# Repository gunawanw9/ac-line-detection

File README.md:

# [AC mains/ Zero Crossing Detection Module](https://shop.edwinrobotics.com/sensors/960-ac-mains-zero-crossing-detection-module.html) #

The AC mains/ Zero Crossing Detection Module from Edwin Robotics is an optically isolated AC line-to-logic interface device. The AC line voltage is monitored by a rectifier and an optocoupler, which provides isolation between High Voltage (HV) and Low Voltage (LV) Side. An active AC power line drives the output gate of the optocoupler to a logic low condition and in the absence of an AC line the output remains HIGH. The board is designed solely for the use as an AC line monitor. By default the output of the optocoupler is connected to a 2.2uF capacitor to provide TTL output, in the event that zero crossing is required, a jumper trace on the back of the PCB will need to be cut. Check the hookup guide for more information. The board has an on board pull-up resistors for uses with microcontrollers with weak pull-up. 

**FEATURES:**

* AC mains & Zero Crossing detection.
* On board pull-up
* High voltage isolation between input and output.
* Logic level compatibility

**SPECIFICATION:**

* Input Voltage Range: 110-300 V AC
* Max. Output Voltage Range: 5V
* Logic Interface: VCC, GND, Signal
* Dimensions: 20x20mm

**DOCUMENTS:**

[Hookup Guide](http://learn.edwinrobotics.com/230v110v-ac-mains-detection-using-arduino-raspberry-pi-and-esp8266-thing/)

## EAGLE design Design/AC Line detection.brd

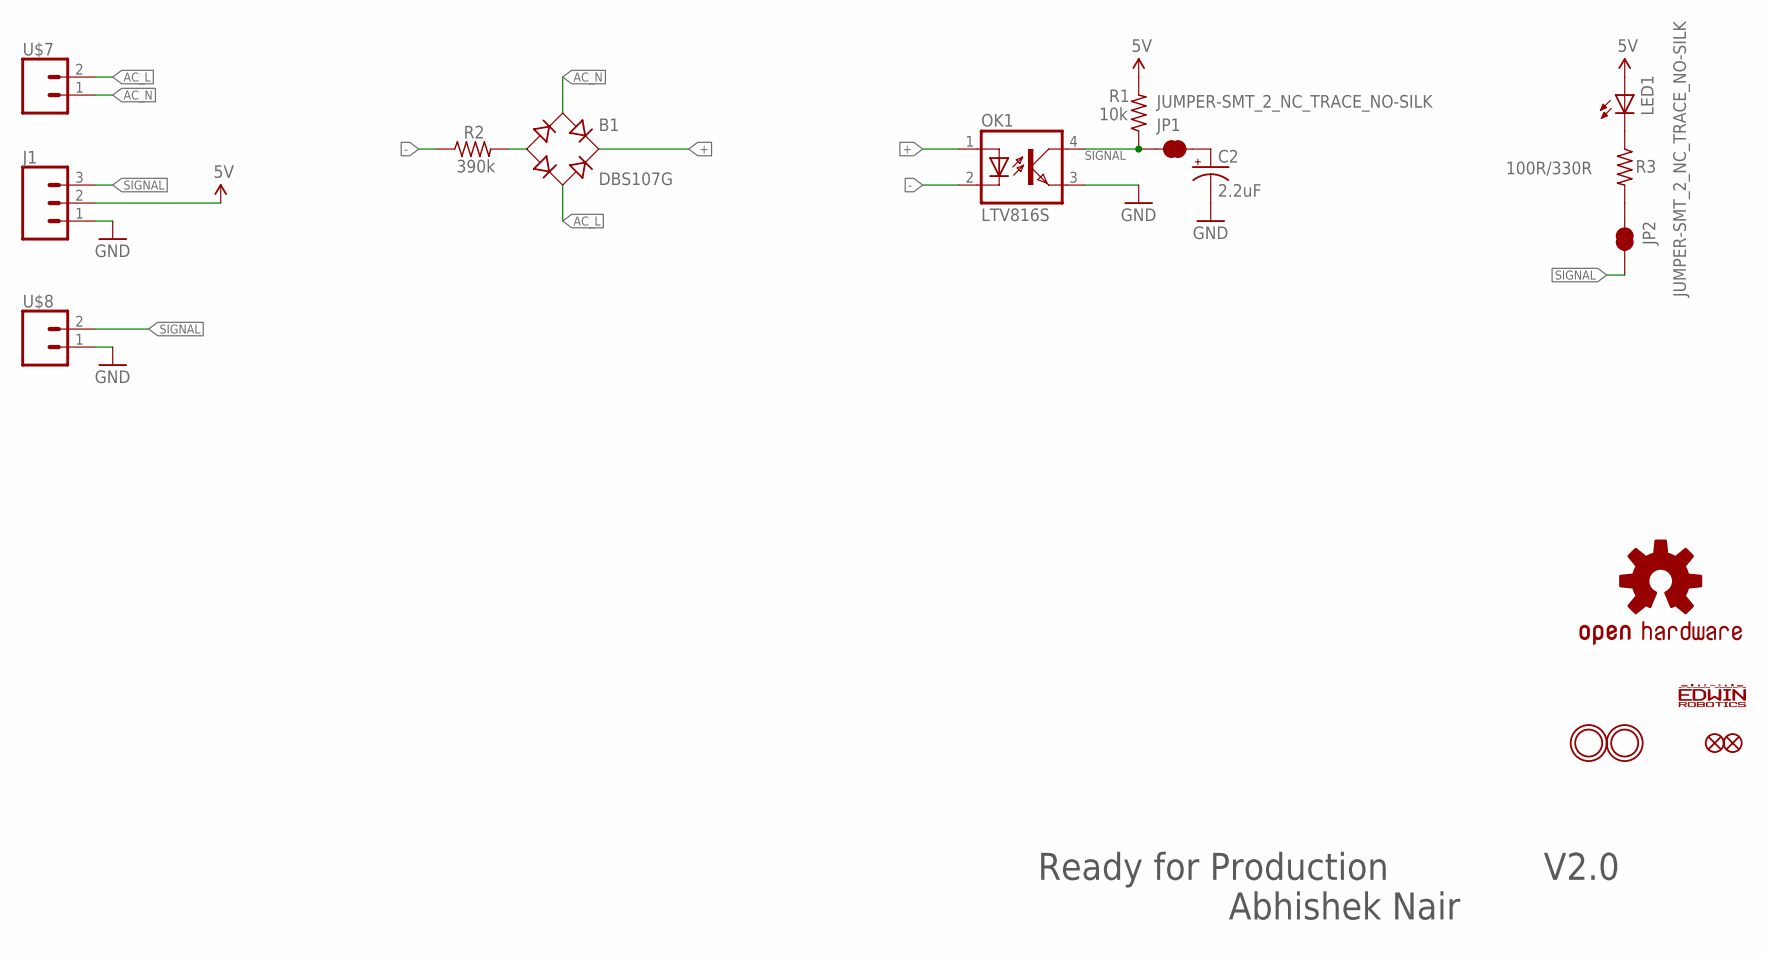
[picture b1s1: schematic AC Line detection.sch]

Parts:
B1: DBS107G; DBS
C2: 2.2uF; CAPACITOR-2.2UF_4X5MM_JENNY
FID1, FID2: FIDUCIAL""; FIDUCIAL_1MM
J1: CONN_03; 1X03
JP1, JP2: JUMPER-SMT_2_NC_TRACE_NO-SILK; SMT-JUMPER_2_NC_TRACE_NO-SILK
LED1: LED_TH/SMDCHIPLED_0603; CHIPLED_0603
LOGO1: OSHW-LOGOMINI; OSHW-LOGO-MINI
OK1: LTV816S; DIL4-SMD
R1: 10k; R0603
R2: 390k; R0603
R3: 100R/330R; R0603
U$1: LOGO-9.5MMX4.5MM
U$5, U$6: MOUNTINGHOLE3.0THIN; MOUNTINGHOLE_3.0_PLATEDTHIN
U$7, U$8: SCREW_TERMINALS-2P-5MM; W237-102

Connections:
5V: J1.2, LED1.A, R1.2
+: B1.+, OK1.1 (A)
-: OK1.2 (C), R2.1
AC_L: B1.AC2, U$7.2
AC_N: B1.AC1, U$7.1
GND: C2.-, J1.1, OK1.3 (EMIT), U$8.1
unnamed: B1.-, R2.2
unnamed: C2.+, JP1.2
unnamed: LED1.C, R3.1
unnamed: JP2.1, R3.2
SIGNAL: J1.3, JP1.1, JP2.2, OK1.4 (COL), R1.1, U$8.2

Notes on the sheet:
Ready for Production
V2.0
Abhishek Nair

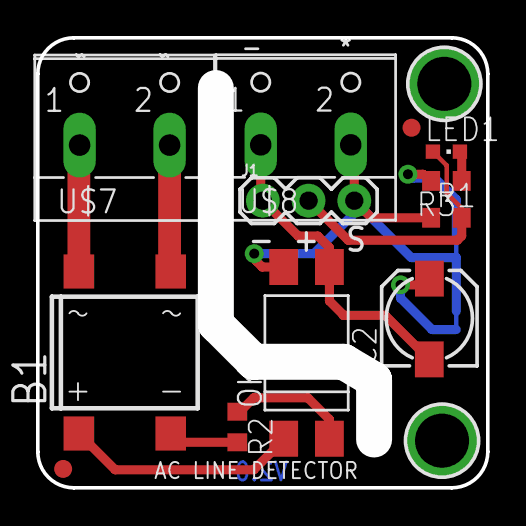
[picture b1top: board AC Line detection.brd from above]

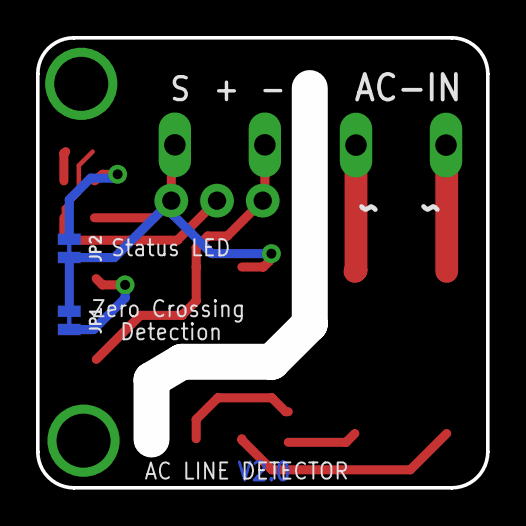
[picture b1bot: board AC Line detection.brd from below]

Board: 2 copper layers, 25.0 x 25.0 mm, 18 parts (4 on the bottom side), 11 nets.

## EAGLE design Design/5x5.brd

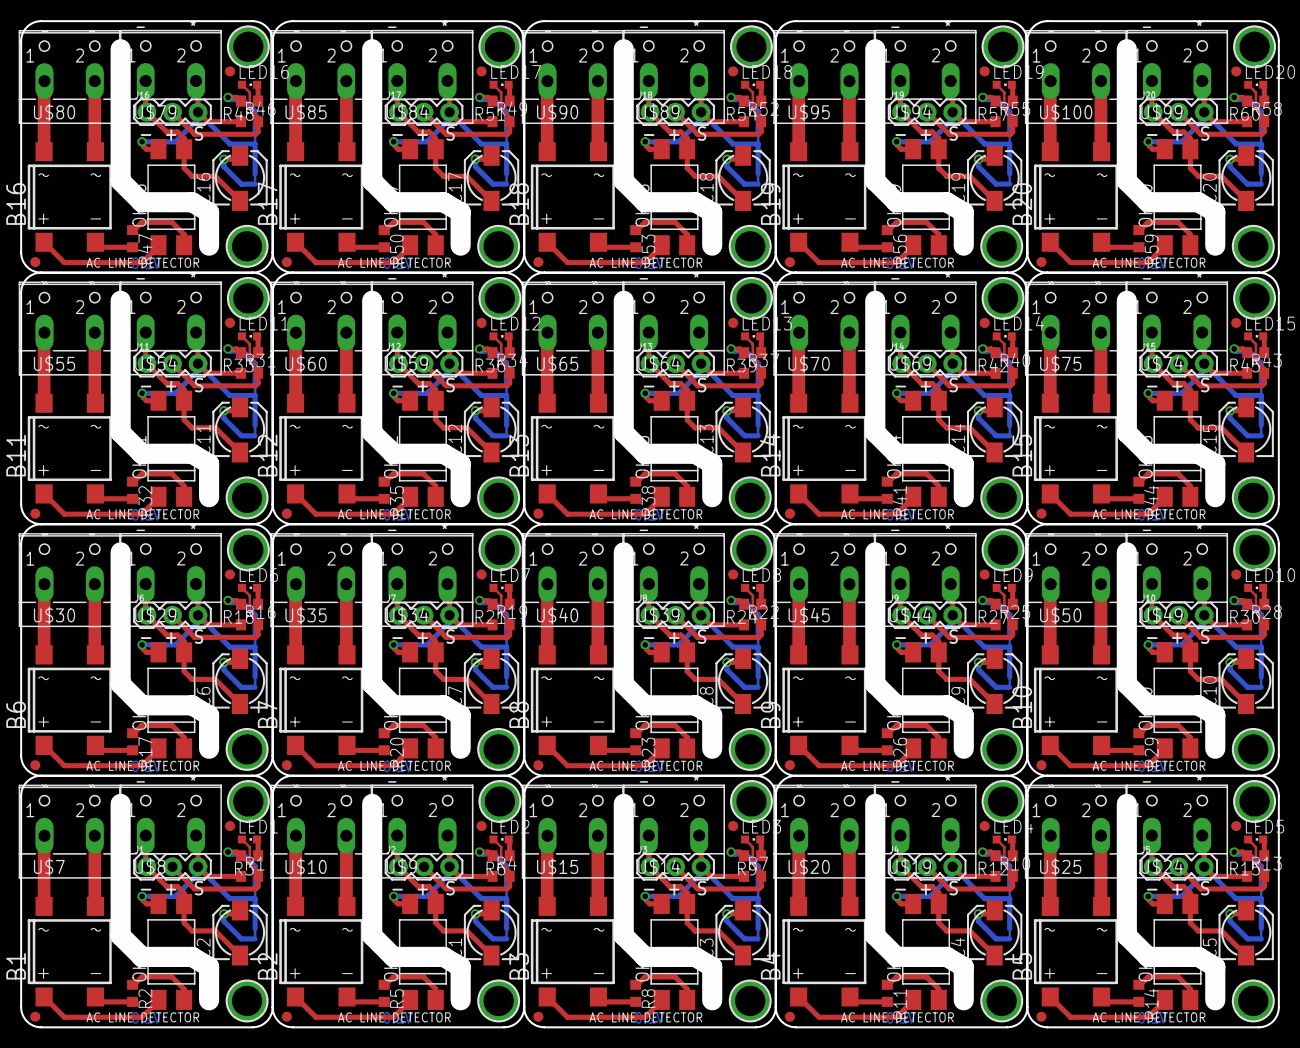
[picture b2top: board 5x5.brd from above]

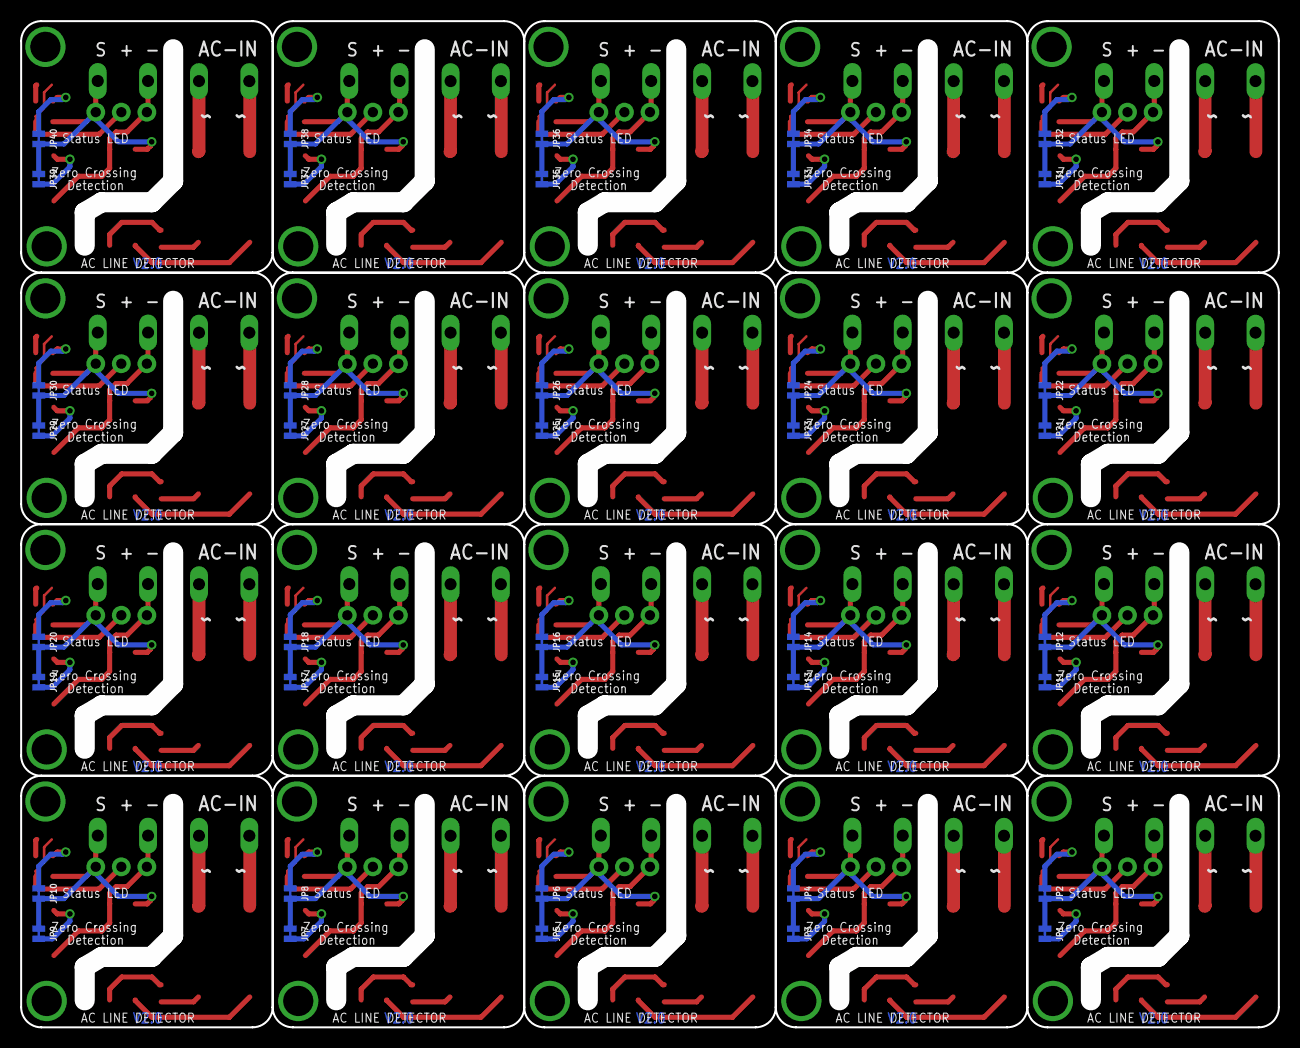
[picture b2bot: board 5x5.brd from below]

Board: 2 copper layers, 125.0 x 100.0 mm, 360 parts (80 on the bottom side), 220 nets.

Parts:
B1, B2, B3, B4, B5, B6, B7, B8, B9, B10, B11, B12, B13, B14, B15, B16, B17, B18, B19, B20: DBS107G; DBS
C1, C2, C3, C4, C5, C6, C7, C8, C9, C10, C11, C12, C13, C14, C15, C16, C17, C18, C19, C20: 2.2uF; CAPACITOR-2.2UF_4X5MM_JENNY
FID1, FID2, FID3, FID4, FID5, FID6, FID7, FID8, FID9, FID10, FID11, FID12, FID13, FID14, FID15, FID16, FID17, FID18, FID19, FID20, FID21, FID22, FID23, FID24, FID25, FID26, FID27, FID28, FID29, FID30, FID31, FID32, FID33, FID34, FID35, FID36, FID37, FID38, FID39, FID40: FIDUCIAL""; FIDUCIAL_1MM
J1, J2, J3, J4, J5, J6, J7, J8, J9, J10, J11, J12, J13, J14, J15, J16, J17, J18, J19, J20: 1X03
JP1, JP2, JP3, JP4, JP5, JP6, JP7, JP8, JP9, JP10, JP11, JP12, JP13, JP14, JP15, JP16, JP17, JP18, JP19, JP20, JP21, JP22, JP23, JP24, JP25, JP26, JP27, JP28, JP29, JP30, JP31, JP32, JP33, JP34, JP35, JP36, JP37, JP38, JP39, JP40: JUMPER-SMT_2_NC_TRACE_NO-SILK; SMT-JUMPER_2_NC_TRACE_NO-SILK
LED1, LED2, LED3, LED4, LED5, LED6, LED7, LED8, LED9, LED10, LED11, LED12, LED13, LED14, LED15, LED16, LED17, LED18, LED19, LED20: CHIPLED_0603
LOGO1, LOGO2, LOGO3, LOGO4, LOGO5, LOGO6, LOGO7, LOGO8, LOGO9, LOGO10, LOGO11, LOGO12, LOGO13, LOGO14, LOGO15, LOGO16, LOGO17, LOGO18, LOGO19, LOGO20: OSHW-LOGOMINI; OSHW-LOGO-MINI
OK1, OK2, OK3, OK4, OK5, OK6, OK7, OK8, OK9, OK10, OK11, OK12, OK13, OK14, OK15, OK16, OK17, OK18, OK19, OK20: LTV816S; DIL4-SMD
R1, R4, R7, R10, R13, R16, R19, R22, R25, R28, R31, R34, R37, R40, R43, R46, R49, R52, R55, R58: 10k; R0603
R2, R5, R8, R11, R14, R17, R20, R23, R26, R29, R32, R35, R38, R41, R44, R47, R50, R53, R56, R59: 390k; R0603
R3, R6, R9, R12, R15, R18, R21, R24, R27, R30, R33, R36, R39, R42, R45, R48, R51, R54, R57, R60: 100R/330R; R0603
U$1, U$2, U$11, U$16, U$21, U$26, U$31, U$36, U$41, U$46, U$51, U$56, U$61, U$66, U$71, U$76, U$81, U$86, U$91, U$96: LOGO-9.5MMX4.5MM
U$3, U$4, U$5, U$6, U$12, U$13, U$17, U$18, U$22, U$23, U$27, U$28, U$32, U$33, U$37, U$38, U$42, U$43, U$47, U$48, U$52, U$53, U$57, U$58, U$62, U$63, U$67, U$68, U$72, U$73, U$77, U$78, U$82, U$83, U$87, U$88, U$92, U$93, U$97, U$98: MOUNTINGHOLE3.0THIN; MOUNTINGHOLE_3.0_PLATEDTHIN
U$7, U$8, U$9, U$10, U$14, U$15, U$19, U$20, U$24, U$25, U$29, U$30, U$34, U$35, U$39, U$40, U$44, U$45, U$49, U$50, U$54, U$55, U$59, U$60, U$64, U$65, U$69, U$70, U$74, U$75, U$79, U$80, U$84, U$85, U$89, U$90, U$94, U$95, U$99, U$100: SCREW_TERMINALS-2P-5MM; W237-102

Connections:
5V: J1.2, LED1.A, R1.2
5V1: J2.2, LED2.A, R4.2
5V2: J3.2, LED3.A, R7.2
5V3: J4.2, LED4.A, R10.2
5V4: J5.2, LED5.A, R13.2
5V5: J6.2, LED6.A, R16.2
5V6: J7.2, LED7.A, R19.2
5V7: J8.2, LED8.A, R22.2
5V8: J9.2, LED9.A, R25.2
5V9: J10.2, LED10.A, R28.2
5V10: J11.2, LED11.A, R31.2
5V11: J12.2, LED12.A, R34.2
5V12: J13.2, LED13.A, R37.2
5V13: J14.2, LED14.A, R40.2
5V14: J15.2, LED15.A, R43.2
5V15: J16.2, LED16.A, R46.2
5V16: J17.2, LED17.A, R49.2
5V17: J18.2, LED18.A, R52.2
5V18: J19.2, LED19.A, R55.2
5V19: J20.2, LED20.A, R58.2
+: B1.+, OK1.1
+1: B2.+, OK2.1
+2: B3.+, OK3.1
+3: B4.+, OK4.1
+4: B5.+, OK5.1
+5: B6.+, OK6.1
+6: B7.+, OK7.1
+7: B8.+, OK8.1
+8: B9.+, OK9.1
+9: B10.+, OK10.1
+10: B11.+, OK11.1
+11: B12.+, OK12.1
+12: B13.+, OK13.1
+13: B14.+, OK14.1
+14: B15.+, OK15.1
+15: B16.+, OK16.1
+16: B17.+, OK17.1
+17: B18.+, OK18.1
+18: B19.+, OK19.1
+19: B20.+, OK20.1
-: OK1.2, R2.1
-1: OK2.2, R5.1
-2: OK3.2, R8.1
-3: OK4.2, R11.1
-4: OK5.2, R14.1
-5: OK6.2, R17.1
-6: OK7.2, R20.1
-7: OK8.2, R23.1
-8: OK9.2, R26.1
-9: OK10.2, R29.1
-10: OK11.2, R32.1
-11: OK12.2, R35.1
-12: OK13.2, R38.1
-13: OK14.2, R41.1
-14: OK15.2, R44.1
-15: OK16.2, R47.1
-16: OK17.2, R50.1
-17: OK18.2, R53.1
-18: OK19.2, R56.1
-19: OK20.2, R59.1
AC_L: B1.AC2, U$7.2
AC_L1: B2.AC2, U$10.2
AC_L2: B3.AC2, U$15.2
AC_L3: B4.AC2, U$20.2
AC_L4: B5.AC2, U$25.2
AC_L5: B6.AC2, U$30.2
AC_L6: B7.AC2, U$35.2
AC_L7: B8.AC2, U$40.2
AC_L8: B9.AC2, U$45.2
AC_L9: B10.AC2, U$50.2
AC_L10: B11.AC2, U$55.2
AC_L11: B12.AC2, U$60.2
AC_L12: B13.AC2, U$65.2
AC_L13: B14.AC2, U$70.2
AC_L14: B15.AC2, U$75.2
AC_L15: B16.AC2, U$80.2
AC_L16: B17.AC2, U$85.2
AC_L17: B18.AC2, U$90.2
AC_L18: B19.AC2, U$95.2
AC_L19: B20.AC2, U$100.2
AC_N: B1.AC1, U$7.1
AC_N1: B2.AC1, U$10.1
AC_N2: B3.AC1, U$15.1
AC_N3: B4.AC1, U$20.1
AC_N4: B5.AC1, U$25.1
AC_N5: B6.AC1, U$30.1
AC_N6: B7.AC1, U$35.1
AC_N7: B8.AC1, U$40.1
AC_N8: B9.AC1, U$45.1
AC_N9: B10.AC1, U$50.1
AC_N10: B11.AC1, U$55.1
AC_N11: B12.AC1, U$60.1
AC_N12: B13.AC1, U$65.1
AC_N13: B14.AC1, U$70.1
AC_N14: B15.AC1, U$75.1
AC_N15: B16.AC1, U$80.1
AC_N16: B17.AC1, U$85.1
AC_N17: B18.AC1, U$90.1
AC_N18: B19.AC1, U$95.1
AC_N19: B20.AC1, U$100.1
GND: C2.-, J1.1, OK1.3, U$8.1
GND1: C1.-, J2.1, OK2.3, U$9.1
GND2: C3.-, J3.1, OK3.3, U$14.1
GND3: C4.-, J4.1, OK4.3, U$19.1
GND4: C5.-, J5.1, OK5.3, U$24.1
GND5: C6.-, J6.1, OK6.3, U$29.1
GND6: C7.-, J7.1, OK7.3, U$34.1
GND7: C8.-, J8.1, OK8.3, U$39.1
GND8: C9.-, J9.1, OK9.3, U$44.1
GND9: C10.-, J10.1, OK10.3, U$49.1
GND10: C11.-, J11.1, OK11.3, U$54.1
GND11: C12.-, J12.1, OK12.3, U$59.1
GND12: C13.-, J13.1, OK13.3, U$64.1
GND13: C14.-, J14.1, OK14.3, U$69.1
GND14: C15.-, J15.1, OK15.3, U$74.1
GND15: C16.-, J16.1, OK16.3, U$79.1
GND16: C17.-, J17.1, OK17.3, U$84.1
GND17: C18.-, J18.1, OK18.3, U$89.1
GND18: C19.-, J19.1, OK19.3, U$94.1
GND19: C20.-, J20.1, OK20.3, U$99.1
unnamed: B1.-, R2.2
unnamed: C2.+, JP1.2
unnamed: LED1.C, R3.1
unnamed: JP2.1, R3.2
unnamed: B2.-, R5.2
unnamed: C1.+, JP3.2
unnamed: JP4.1, R6.2
unnamed: LED2.C, R6.1
unnamed: B3.-, R8.2
unnamed: C3.+, JP5.2
unnamed: JP6.1, R9.2
unnamed: LED3.C, R9.1
unnamed: B4.-, R11.2
unnamed: C4.+, JP7.2
unnamed: JP8.1, R12.2
unnamed: LED4.C, R12.1
unnamed: B5.-, R14.2
unnamed: C5.+, JP9.2
unnamed: JP10.1, R15.2
unnamed: LED5.C, R15.1
unnamed: B6.-, R17.2
unnamed: C6.+, JP11.2
unnamed: JP12.1, R18.2
unnamed: LED6.C, R18.1
unnamed: B7.-, R20.2
unnamed: C7.+, JP13.2
unnamed: JP14.1, R21.2
unnamed: LED7.C, R21.1
unnamed: B8.-, R23.2
unnamed: C8.+, JP15.2
unnamed: JP16.1, R24.2
unnamed: LED8.C, R24.1
unnamed: B9.-, R26.2
unnamed: C9.+, JP17.2
unnamed: JP18.1, R27.2
unnamed: LED9.C, R27.1
unnamed: B10.-, R29.2
unnamed: C10.+, JP19.2
unnamed: JP20.1, R30.2
unnamed: LED10.C, R30.1
unnamed: B11.-, R32.2
unnamed: C11.+, JP21.2
unnamed: JP22.1, R33.2
unnamed: LED11.C, R33.1
unnamed: B12.-, R35.2
unnamed: C12.+, JP23.2
unnamed: JP24.1, R36.2
unnamed: LED12.C, R36.1
unnamed: B13.-, R38.2
unnamed: C13.+, JP25.2
unnamed: JP26.1, R39.2
unnamed: LED13.C, R39.1
unnamed: B14.-, R41.2
unnamed: C14.+, JP27.2
unnamed: JP28.1, R42.2
unnamed: LED14.C, R42.1
unnamed: B15.-, R44.2
unnamed: C15.+, JP29.2
unnamed: JP30.1, R45.2
unnamed: LED15.C, R45.1
unnamed: B16.-, R47.2
unnamed: C16.+, JP31.2
unnamed: JP32.1, R48.2
unnamed: LED16.C, R48.1
unnamed: B17.-, R50.2
unnamed: C17.+, JP33.2
unnamed: JP34.1, R51.2
unnamed: LED17.C, R51.1
unnamed: B18.-, R53.2
unnamed: C18.+, JP35.2
unnamed: JP36.1, R54.2
unnamed: LED18.C, R54.1
unnamed: B19.-, R56.2
unnamed: C19.+, JP37.2
unnamed: JP38.1, R57.2
unnamed: LED19.C, R57.1
unnamed: B20.-, R59.2
unnamed: C20.+, JP39.2
unnamed: JP40.1, R60.2
unnamed: LED20.C, R60.1
SIGNAL: J1.3, JP1.1, JP2.2, OK1.4, R1.1, U$8.2
SIGNAL1: J2.3, JP3.1, JP4.2, OK2.4, R4.1, U$9.2
SIGNAL2: J3.3, JP5.1, JP6.2, OK3.4, R7.1, U$14.2
SIGNAL3: J4.3, JP7.1, JP8.2, OK4.4, R10.1, U$19.2
SIGNAL4: J5.3, JP9.1, JP10.2, OK5.4, R13.1, U$24.2
SIGNAL5: J6.3, JP11.1, JP12.2, OK6.4, R16.1, U$29.2
SIGNAL6: J7.3, JP13.1, JP14.2, OK7.4, R19.1, U$34.2
SIGNAL7: J8.3, JP15.1, JP16.2, OK8.4, R22.1, U$39.2
SIGNAL8: J9.3, JP17.1, JP18.2, OK9.4, R25.1, U$44.2
SIGNAL9: J10.3, JP19.1, JP20.2, OK10.4, R28.1, U$49.2
SIGNAL10: J11.3, JP21.1, JP22.2, OK11.4, R31.1, U$54.2
SIGNAL11: J12.3, JP23.1, JP24.2, OK12.4, R34.1, U$59.2
SIGNAL12: J13.3, JP25.1, JP26.2, OK13.4, R37.1, U$64.2
SIGNAL13: J14.3, JP27.1, JP28.2, OK14.4, R40.1, U$69.2
SIGNAL14: J15.3, JP29.1, JP30.2, OK15.4, R43.1, U$74.2
SIGNAL15: J16.3, JP31.1, JP32.2, OK16.4, R46.1, U$79.2
SIGNAL16: J17.3, JP33.1, JP34.2, OK17.4, R49.1, U$84.2
SIGNAL17: J18.3, JP35.1, JP36.2, OK18.4, R52.1, U$89.2
SIGNAL18: J19.3, JP37.1, JP38.2, OK19.4, R55.1, U$94.2
SIGNAL19: J20.3, JP39.1, JP40.2, OK20.4, R58.1, U$99.2

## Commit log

2017-06-08 Version 1.0
    Tested Circuit and Design
2017-06-12 version 1.0
    * Added production files
2017-06-13 Version 1.0
    * updated schematics: Added electrolytic capacitor on board
    * Updated board: increased dimesnions and new routing
2017-06-13 version 1.0 update:
    * Updated Capacitor Pad Size
2017-07-09 README.md edited online with Bitbucket
2017-07-09 *Removed production files* *Added Licesence and readme file*
2017-07-09 *Version 1.0 : Added Production Files*
2017-07-09 *Updated Licesence file*
2017-07-09 LICESENCE.md edited online with Bitbucket
2017-07-10 Updated License file
2018-03-29 Version 2.0:
    Major Changes:
    *Updated Design FIles
    * Updated the board Size
    * Added mounting Holes
    * Added Debug LED and enable/Disbale Jumper
    * Replaced Screw terminal with KF126
2018-05-24 Version 2.0: Added Gerber Files
